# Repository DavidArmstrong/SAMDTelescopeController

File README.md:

# SAMDTelescopeController

## Arduino SAMD51-based Telescope Controller 4.00.00

### Main Repository Readme File

#### By David Armstrong, December 2025
 - See MIT LICENSE file

========================================================================

Note: This project is unfinished, although most of the work has been done.  I'm making it public 
so others can build on this framework. I'll continue to improve it, as I'm able to squeeze out
a few precious milliseconds over the coming months and years.

This repository implements one of many possible design scenarios for a Telescope Controller, 
using the Arduino IDE as a development environment.  It's purpose is to allow me, personally,
to use my telescope to look at stuff, instead of spending a lot of time setting it up.

I'm making this available for others to use as a reference in designing their own systems.  As
such, feel free to clone it and change as your needs dictate.

## Organization of the Repository

There are several directories in this project, each containing relevant information and code:

 - docs : Contains nearly all related documentation files for the system. (The Arduino sketches have their own Readme files.) There is a Draw.io based PNG image file showing the basic buiding blocks that make up the system, and how all the parts communicate with each other.
 - Arduino_Telescope_Interface : Eagle schematic of how to connect various interfaces.  If you have the Eagle PCB software installed, this directory should be copied to be a subdirectory under the EAGLE/projects/ directory.
 - TC4_0diagnostics : Arduino sketch designed to be used as a precursor sketch to TC4_0.  It's purpose is to help make sure all the needed software libraries are installed, and that the associated required hardware is present and working. (Completed)
 - TC4_0 : Arduino SAMD51 processor based Telescope Controller 4.00.00 sketch, that is the Telescope Controller program itself. (Still under development)
 
 Most of these have their own Readme file, and should be referenced in the order listed above, as each has
 information relevant to documents that follow them in the list.
 
 Here is a diagram of how the various hardware components relate to each other:

 <object data="Arduino_Telescope_Interface/Telescope_Interface_shield.pdf" type="application/pdf" width="700px" height="700px">
    <embed src="Arduino_Telescope_Interface/Telescope_Interface_shield.pdf">
        <p>Please download the Hardware Schematic PDF to view it: <a href="Arduino_Telescope_Interface/Telescope_Interface_shield.pdf">Hardware Schematic PDF</a>.</p>
    </embed>
</object>

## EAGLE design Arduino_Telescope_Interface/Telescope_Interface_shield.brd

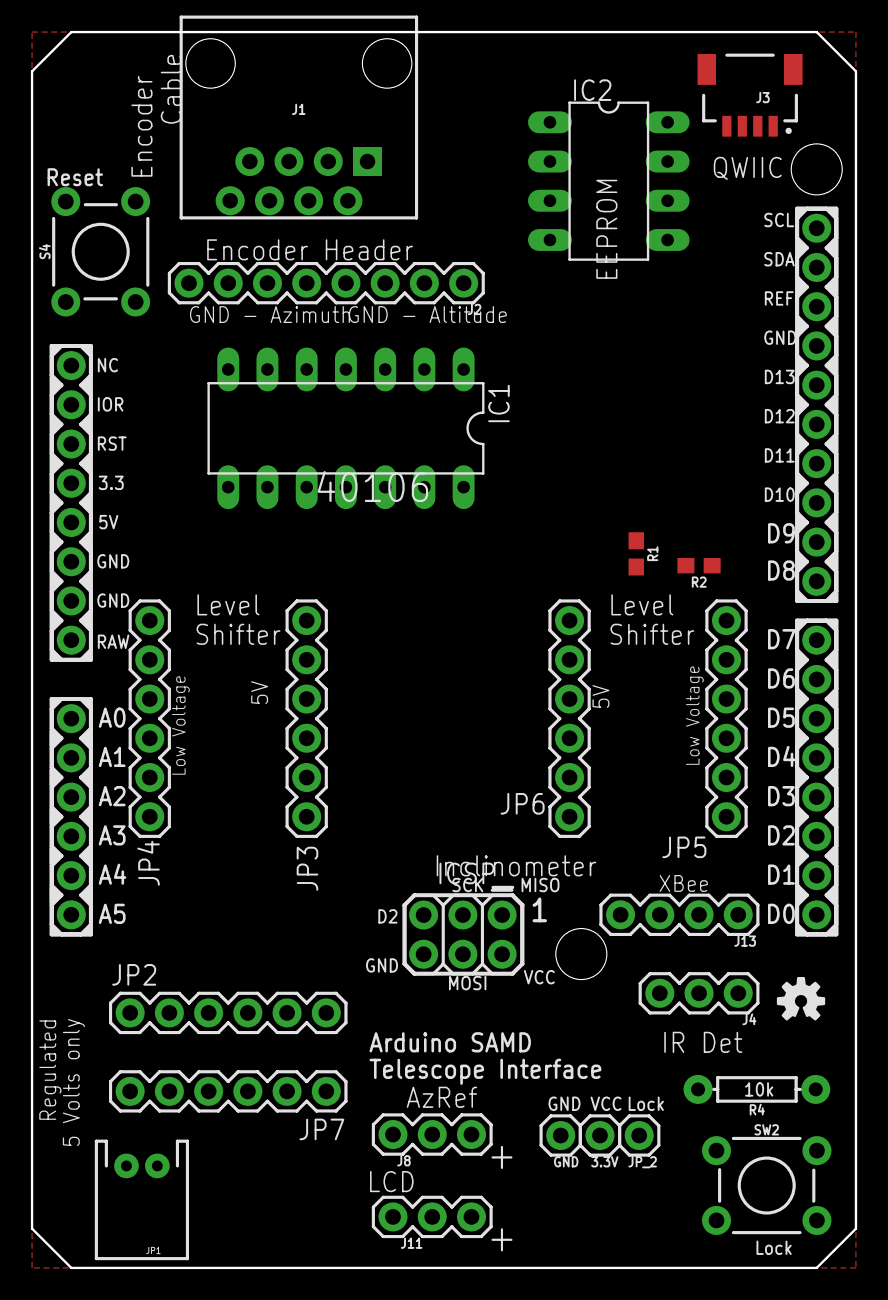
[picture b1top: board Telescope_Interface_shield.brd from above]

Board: 2 copper layers, 53.3 x 80.0 mm, 28 parts (0 on the bottom side), 35 nets, no tracks yet.

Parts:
3.3V: 1X01
FRAME1: FRAME-LETTER; CREATIVE_COMMONS
GND: 1X01
IC1: 40106N; DIL14
IC2: 24LC256P; DIL8
ICSP: ICSP; 2X3
J1: RJ45; RJ45-8
J2: 1X08
J3: JST04_1MM_RA
J4, J8, J11: 455-1750-1-ND; 1X03
J13: 1X04
JP1: JST-2-PTH
JP2, JP3, JP4, JP5, JP6, JP7: 1X06
JP8: ARDUINO_R3_SHIELDR3_PROTO_SHIELD; UNO_R3_PROTO_SHIELD
JP_2: 1X01
LOGO1: OSHW-LOGOS; OSHW-LOGO-S
R1, R2: 4.7k; 0603
R4: 10k; AXIAL-0.3
S4: MOMENTARY-SWITCH-SPST-PTH-6.0MM; TACTILE_SWITCH_PTH_6.0MM
SW2: MOMENTARY-SWITCH-SPST-PTH-6.0MM; TACTILE_SWITCH_PTH_6.0MM

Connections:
3.3V: 3.3V.1, IC2.8, ICSP.2, J3.2, J4.1, J13.1, JP2.2, JP4.4, JP5.4, JP7.5, JP8.3.3V, R1.2, R2.2, R4.P$2
5V: IC1.14, J1.2, J1.6, J2.2, J2.6, J8.1, J11.2, JP1.2, JP3.3, JP6.3, JP8.5V
A1: JP4.6, JP8.A1
A2: JP4.5, JP8.A2
A3: JP4.2, JP8.A3
A4: JP4.1, JP8.A4
A5: JP8.A5, JP_2.1, R4.P$1, SW2.3
AL_A: IC1.4, JP3.5
AL_B: IC1.2, JP3.6
AZREF: IC1.11, J8.3
AZ_A: IC1.6, JP3.2
AZ_B: IC1.8, JP3.1
D4: J13.3, JP8.D4
D5: JP5.5, JP8.D5
D6: JP5.2, JP8.D6
D7: J13.4, JP8.D7
D8: JP5.6, JP8.D8
D9: JP7.3, JP8.D9, R2.1
D10: JP2.4, JP8.D10, R1.1
D11: J4.2, JP8.D11
GND: GND.1, IC1.7, IC2.1, IC2.2, IC2.3, IC2.4, ICSP.6, J1.4, J1.8, J2.4, J2.8, J3.1, J4.3, J8.2, J11.1, J13.2, JP1.1, JP2.3, JP3.4, JP4.3, JP5.3, JP6.4, JP7.4, JP8.GND@0, JP8.GND@1, JP8.GND@2, S4.1, SW2.1
HV1: IC1.10, JP6.1
HV2: IC1.12, JP6.2
LCD: J11.3, JP6.6
MISO: ICSP.1, JP2.5, JP7.2
MOSI: ICSP.4, JP2.6, JP7.1
unnamed: IC1.3, J1.1, J2.1
unnamed: IC1.1, J1.3, J2.3
unnamed: IC1.5, J1.7, J2.7
unnamed: IC1.9, J1.5, J2.5
RESET: JP8.RES, S4.3
SCK: ICSP.3, JP2.1, JP7.6
SCL: IC2.6, J3.4, JP8.SCL
SDA: IC2.5, J3.3, JP8.SDA
TX: JP5.1, JP8.TX

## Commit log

2020-04-25 Initial upload
    Minimal work done at this point.
2021-09-07 Update to 5 Sep 2021
    Has only Terminal code in place, and minus any motor/mount setup.
2022-05-05 Update as of 4 May 2022
    latest update using SamD51, no IR, no serial2
2022-06-05 Update initialization towards final design
    Initialization updated to reflect final design requirements. Added architecture block diagram.
2022-06-12 Add Diagnostics sketch
    Add Diagnostics sketch to assist in set up
2022-06-20 Updated schematic and start motor implementation
    Updated schematic for Metro M4 use and start motor implementation
2022-07-03 Motor driver calls added
    Motor driver calls added and Diagnostics sketch expanded for motor and OLED testing
2022-07-04 Remove old schematic PDF
    Remove old schematic PDF
2022-07-08 Add Magnetic North detection
    Added code to determine magnetic North, which is required for accurate Azimuth positioning when aiming at a celestial target position.
2022-07-12 Motor Update 1
    General update with some motor implementation, docs updated, etc.
2022-07-12 FIx readme file
2022-08-06 Speed Update for Terminal display
    Only check for GPS update once per minute, to prevent loading I2C too much. Diagram updated with more complete and consistent info. Some more motor support added.
2022-08-06 Update Readme to show code sections
    Update Readme to show code sections
2022-08-06 Second attempt at readme update
    Second attempt at Readme update
2022-10-15 Correction to interface shield
    Correction to interface shield for Adafruit M4 Metro SAMD51 board that has 5V pin on ICSP connector
2022-11-09 Final Commit to make available
    Final Commit to make available to the public
2023-07-15 First batch of fixes
    Refactor documentation
2023-07-15 Update diagram power cord label
2023-07-15 Various doc corrections
2023-07-15 Update Eagle schematic files
2023-07-15 Rename Eagle directory to Arduino_Telescope_Interface
2023-07-15 Update PDF reference
2023-07-15 Update PDF ref again
2023-07-23 Update StarTweak function
2023-08-05 LCD backlight dim
    LCD backlight dim and bright
2023-08-19 LCDdimmer and brighter syntax fixes
2023-08-19 Update Readme files
2023-08-19 updated diagnostics readme
2023-08-19 fix code change doc in diagnostics readme
2023-08-23 Improved Diagnostics documentation
2023-08-29 More documentation changes, and LCD fixes
2026-02-27 latest changes in design, etc
    Update design to separate out power monitoring. Lots of other stuff too.

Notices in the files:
parts and their libraries:
SparkFun-Aesthetics: Licensing: Creative Commons ShareAlike 4.0 International - https://creativecommons.org/licenses/by-sa/4.0
SparkFun-Aesthetics: Released under the Creative Commons Attribution Share-Alike 4.0 License
SparkFun-Aesthetics: https://creativecommons.org/licenses/by-sa/4.0
